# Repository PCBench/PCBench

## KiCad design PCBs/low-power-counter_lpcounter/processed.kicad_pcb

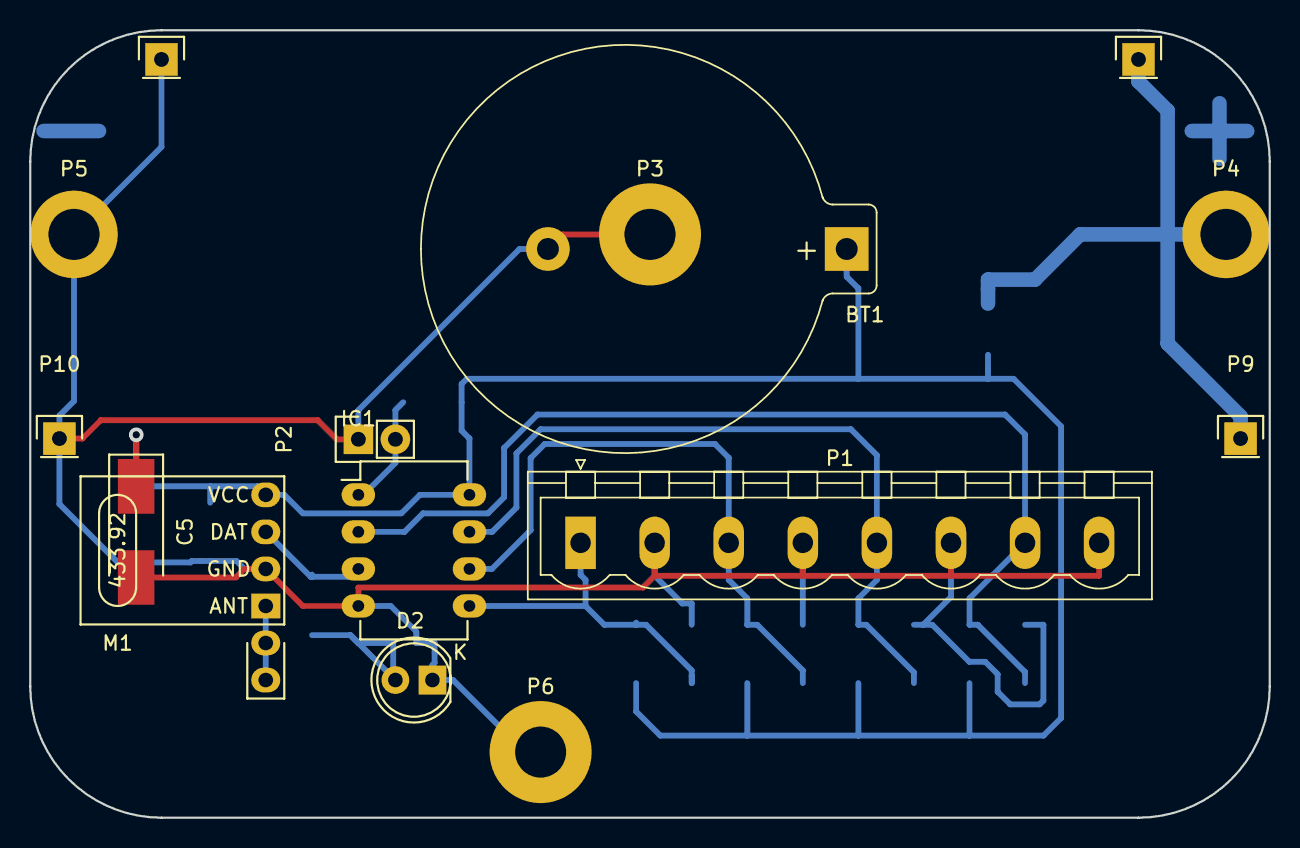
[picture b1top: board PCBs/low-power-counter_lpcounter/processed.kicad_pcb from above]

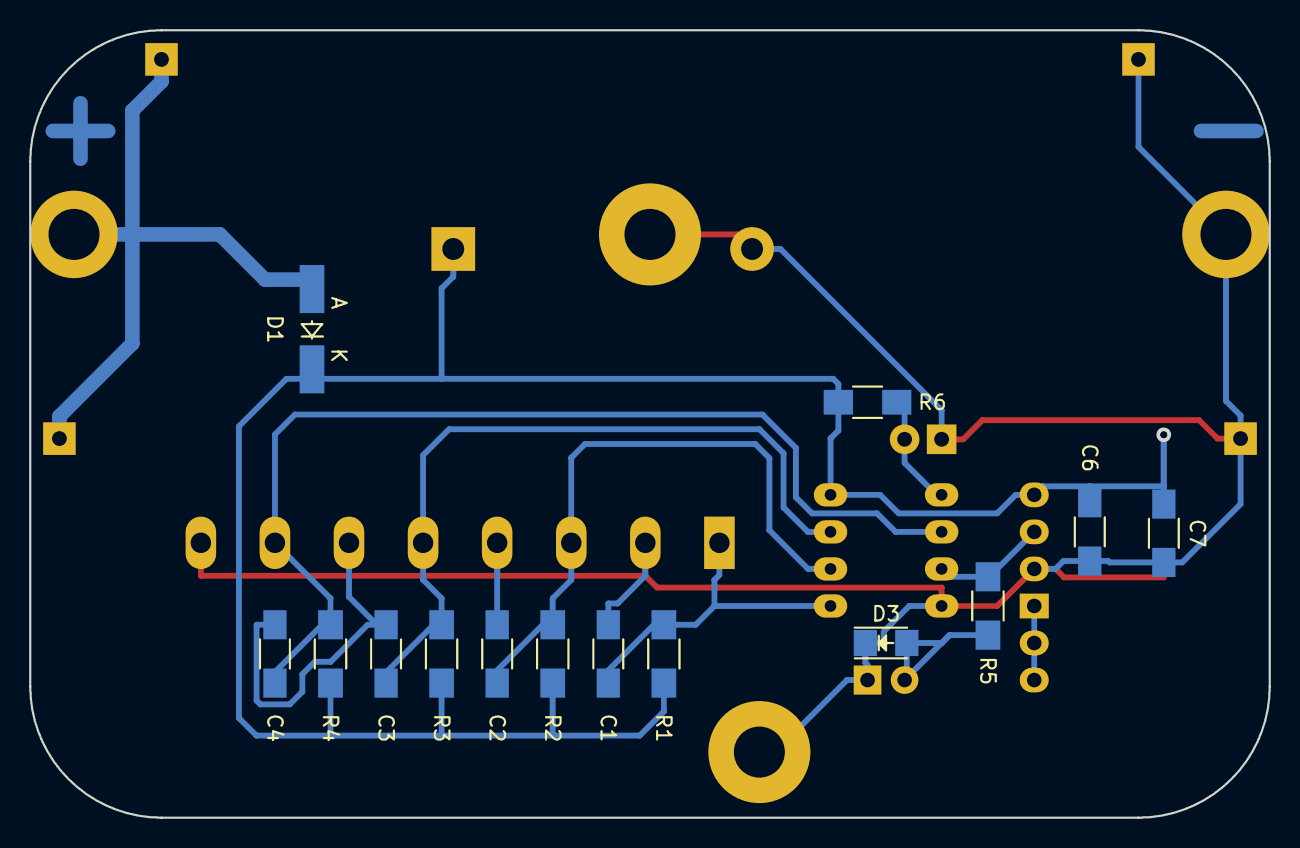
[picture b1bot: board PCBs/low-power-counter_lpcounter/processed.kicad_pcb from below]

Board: 2 copper layers, 85.0 x 54.0 mm, 29 parts (14 on the bottom side), 10 nets.

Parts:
BT1: CR2032; Keystone_106_1x20mm-CoinCell
C1, C2, C3, C4, C6, C7: 100nF; C_1206_HandSoldering
C5: 4.7uF; Tantalum_Case-U_EIA-6032-15_Hand
D1: 1N4148; MiniMELF_Handsoldering
D2: ORANGE; LED-5MM
D3: ORANGE; LED_1206
IC1: ATTINY85V-P; DIP-8_W7.62mm_LongPads
M1: SYN115
P1: CONN_01X08; PhoenixContact_MSTBVA-G_08x5.08mm_Vertical
P2: CONN_02X01; Pin_Header_Straight_1x02
P3, P4, P5, P6: Hole_3.5mm; MountingHole_3.5mm_Pad
P7, P9: BAT+; Pin_Header_Straight_1x01
P8, P10: BAT-; Pin_Header_Straight_1x01
R1, R2, R3, R4: 1M; R_1206_HandSoldering
R5: 1k; R_1206_HandSoldering
R6: 10k; R_1206_HandSoldering

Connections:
+3V3: BT1.1, C5.1, C6.1, C7.1, D1.1, IC1.8, M1.4, R1.1, R2.1, R3.1, R4.1, R6.1
/IN0: C1.1, IC1.5, P1.1, R1.2
/IN1: C2.1, IC1.6, P1.3, R2.2
/IN2: C3.1, IC1.7, P1.5, R3.2
/IN3: C4.1, IC1.2, P1.7, R4.2
/LED: D2.2, D3.2, R5.1
/OUT: IC1.3, M1.3, R5.2
/RESETn: IC1.1, P2.2, R6.2
/VBAT: D1.2, P4.1, P7.1, P9.1
GND: BT1.2, C1.2, C2.2, C3.2, C4.2, C5.2, C6.2, C7.2, D2.1, D3.1, IC1.4, M1.2, P1.2, P1.4, P1.6, P1.8, P2.1, P3.1, P5.1, P6.1, P8.1, P10.1

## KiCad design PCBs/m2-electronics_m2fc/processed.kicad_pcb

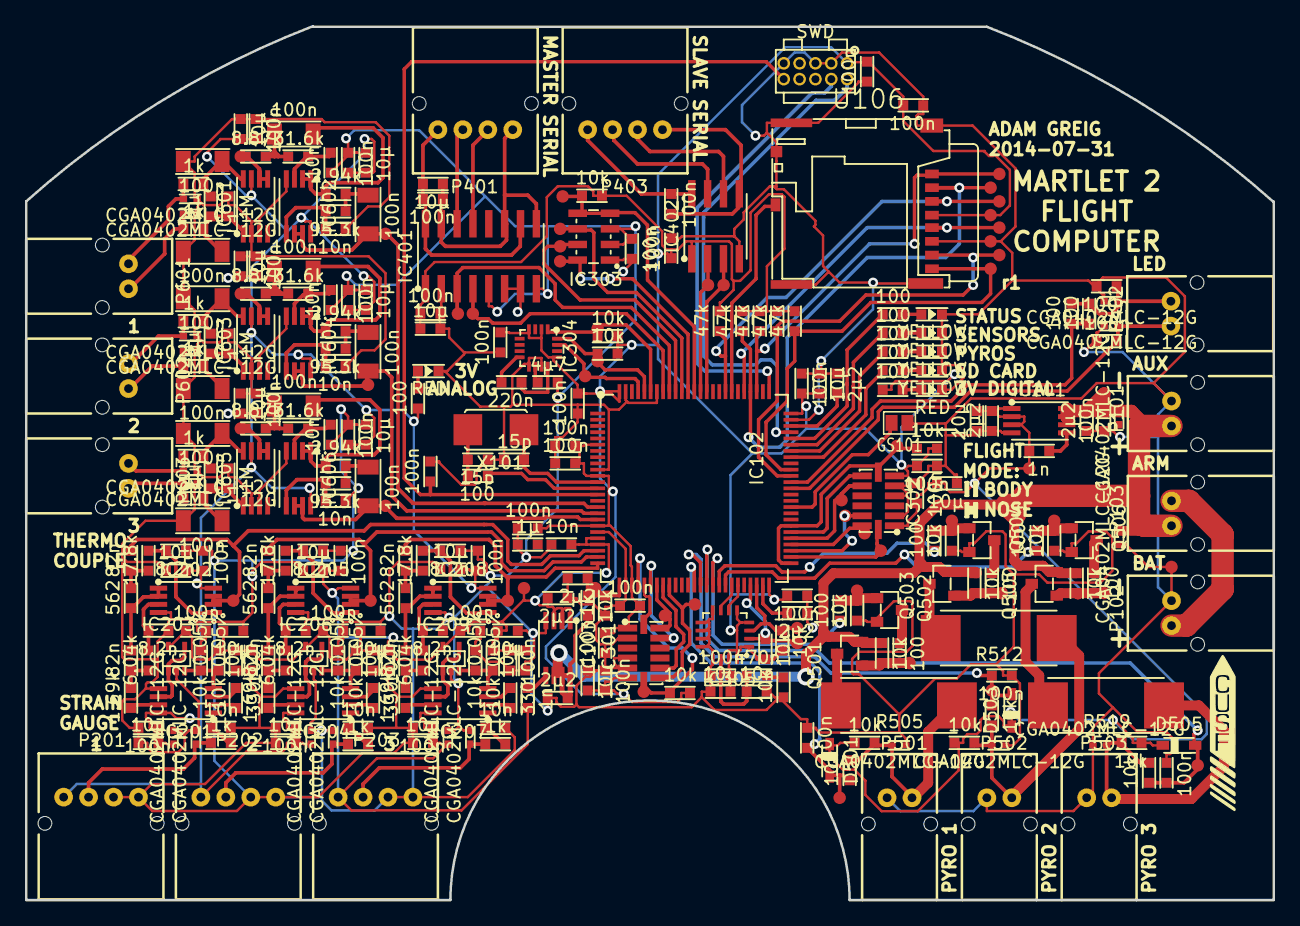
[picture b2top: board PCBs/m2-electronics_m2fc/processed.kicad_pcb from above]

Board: 4 copper layers, 100.0 x 70.0 mm, 345 parts (1 on the bottom side), 170 nets.

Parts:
C101, C104, C106, C119, C120, C124, C126: 2µ2; C0603
C102, C103, C108, C110, C111, C112, C113, C114, C115, C116, C122, C209, C210, C211, C212, C222, C223, C224, C225, C235, C236, C237, C238, C301, C302, C304, C305, C307, C308, C310, C403, C404, C405, C406, C407, C408, C501, C502, C503, C601, C604, C612, C615, C623, C626: 100n; C0603
C105, C125: 1n; C0603
C107, C109, C204, C205, C206, C213, C217, C218, C219, C226, C230, C231, C232, C239, C303, C306, C309, C401, C402, C602, C605, C613, C616, C624, C627: 10µ; C0603
C117, C608, C619, C630: 1µ; C0603
C118, C201, C214, C227, C311, C609, C610, C620, C621, C631, C632: 10n; C0603
C121, C123: 15p; C0603
C202, C203, C215, C216, C228, C229: 82n; C0603
C207, C208, C220, C221, C233, C234: 8.2n; C0603
C312: 220n; C0603
C313: 470n; C0603
C314: 4µ7; C0603
C603, C606, C607, C611, C614, C617, C618, C622, C625, C628, C629, C633: 100n; C1206
D101, D102, D201, D202, D203, D204, D205, D206, D406, D407, D502, D504, D506, D601, D602, D603, D604, D605, D606: CGA0402MLC-12G; R0402
D401, D408: RED; LED0603
D402, D403, D404, D405: YELLOW; LED0603
D501, D503, D505: DIODESCH; SOD323
GS101: GS2
IC101, IC103: ADP3335; MSOP8
IC102: STM32F405VGT; LQFP100
IC201, IC204, IC207: AD8226; MSOP8
IC202, IC205, IC208, IC602, IC604, IC606: AD8656; MSOP8
IC203, IC206, IC209: AD8541; SC-70-5
IC301: ADXL375; ADXL3x5
IC302: ADXL345; ADXL3x5
IC303: MS5611-01BA03; MS5611-01BA
IC304: HMC5883L
IC305: L3G4200D
IC401: ADuM5201; SOIC16
IC402: ADuM1201; SOIC8
IC601, IC603, IC605: AD8495; MSOP8
P101, P102, P103, P402, P501, P502, P503, P601, P602, P603: CONN_2; S02B-PASK-2
P104: SWD; FTSH-105-01-F-D-K
P201, P202, P203, P401, P403: CONN_4; S04B-PASK-2
Q501, Q503, Q505: MOSFET_P; SOT-23-MOSFET
Q502, Q504, Q506: MOSFET_N; SOT-23-MOSFET
R101, R301, R302, R303, R304, R305, R306, R307, R308, R501, R504, R506, R507, R508, R511, R513, R514, R515, R518, R520, R521: 10k; R0603
R102, R201, R209, R217, R601, R606, R608, R613, R615, R620: 1k; R0603
R103, R104, R105, R106, R107: 47k; R0603
R108, R401, R402, R403, R404, R405, R406, R407, R408, R502, R503, R509, R510, R516, R517: 100; R0603
R202, R208, R210, R216, R218, R224: 10k 0.05%; R0603
R203, R211, R219: 330; R0603
R204, R212, R220: 1.69k; R0603
R205, R213, R221: 6.04k; R0603
R206, R214, R222: 562; R0603
R207, R215, R223: 17.8k; R0603
R505, R512, R519: 5; PWR4318
R602, R609, R616: 8.87k; R0603
R603, R610, R617: 31.6k; R0603
R604, R611, R618: 2.94k; R0603
R605, R612, R619: 95.3k; R0603
R607, R614, R621: 1M; R0603
TP101, TP102, TP103, TP104, TP105, TP106, TP107, TP108, TP109, TP110, TP111, TP113, TP114, TP201, TP202, TP203, TP301, TP304, TP305, TP306, TP308, TP309, TP310, TP312, TP313, TP314, TP315, TP316, TP317, TP318, TP319, TP320, TP321, TP401, TP402, TP403, TP404, TP501, TP502, TP503, TP504, TP505, TP506, TP507, TP508, TP509, TP601, TP602, TP603, TP604, TP605, TP606: TESTPAD
U106: MICROSD
U113: LOGO; cusf_logo_full
U114: LOGO; cusf_logo_small
X101: 8M; XTAL50x32

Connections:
+3.3V: C103.1, C105.1, C106.1, C107.1, C108.1, C109.1, C110.1, C111.1, C112.1, C113.1, C114.1, C115.1, C116.1, C301.1, C302.1, C303.1, C304.1, C305.1, C306.1, C307.1, C308.1, C309.1, C310.1, C401.2, C403.2, C406.2, D501.2, D503.2, D505.2, IC101.1, IC101.2, IC101.3, IC102.6, IC102.11, IC102.19, IC102.28, IC102.50, IC102.75, IC102.100, IC301.1, IC301.6, IC302.1, IC302.6, IC303.1, IC304.2, IC304.4, IC304.13, IC305.1, IC305.4, IC305.5, IC305.15, IC305.16, IC401.1, IC401.6, IC401.7, IC402.1, P104.1, R103.1, R104.1, R105.1, R106.1, R107.1, R301.1, R302.1, R303.1, R304.1, R305.1, R306.1, R307.1, R401.2, R506.2, R513.2, R520.2, TP102.1, TP113.1, U106.4
+BATT: C102.1, C104.1, C124.1, D101.1, D102.1, IC101.6, IC101.7, IC101.8, IC103.6, IC103.7, IC103.8, P101.2, P103.2, Q501.S, Q503.S, Q505.S, R101.1, R501.2, R508.2, R515.2, TP104.1
/BAT_MON: C101.2, IC102.26, R101.2, R102.1, TP101.1
/IMU/BARO_CS: IC102.88, IC303.4, IC303.5, R307.2, TP321.1
/IMU/BARO_MISO: IC102.90, IC303.6, TP319.1
/IMU/BARO_MOSI: IC102.91, IC303.7, TP318.1
/IMU/BARO_SCK: IC102.89, IC303.8, TP317.1
/IMU/GYRO_DRDY: IC102.45, IC305.6
/IMU/GYRO_INT1: IC102.44, IC305.7
/IMU/GYRO_SCL: IC102.47, IC305.2, R305.2, TP313.1
/IMU/GYRO_SDA: IC102.48, IC305.3, R303.2, TP315.1
/IMU/HG_ACCEL_CS: IC102.29, IC301.7, R301.2, TP305.1
/IMU/HG_ACCEL_INT1: IC102.34, IC301.8, TP301.1
/IMU/HG_ACCEL_INT2: IC102.33, IC301.9
/IMU/HG_ACCEL_MISO: IC102.31, IC301.12
/IMU/HG_ACCEL_MOSI: IC102.32, IC301.13, TP309.1
/IMU/HG_ACCEL_SCK: IC102.30, IC301.14
/IMU/LG_ACCEL_CS: IC102.51, IC102.57, IC302.7, R302.2, TP306.1
/IMU/LG_ACCEL_INT1: IC102.56, IC302.8
/IMU/LG_ACCEL_INT2: IC102.55, IC302.9, TP304.1
/IMU/LG_ACCEL_MISO: IC102.53, IC302.12, TP308.1
/IMU/LG_ACCEL_MOSI: IC102.54, IC302.13, TP310.1
/IMU/LG_ACCEL_SCK: IC102.52, IC302.14, TP312.1
/IMU/MAGNO_DRDY: IC102.97, IC304.15, TP320.1
/IMU/MAGNO_SCL: IC102.95, IC304.1, R306.2, TP314.1
/IMU/MAGNO_SDA: IC102.96, IC304.16, R304.2, TP316.1
/IO/LED_1: IC102.68, R402.2
/IO/LED_2: IC102.69, R403.2
/IO/LED_3: IC102.70, R404.2
/IO/LED_4: IC102.71, R405.2
/IO/LED_A: IC102.64, R406.2, R407.2
/IO/LED_C: C407.1, D407.2, IC102.63, P402.2
/IO/SER_IN_1: IC102.93, IC401.4, TP402.1
/IO/SER_IN_2: IC102.87, IC402.2, TP403.1
/IO/SER_OUT_1: IC102.92, IC401.3, TP401.1
/IO/SER_OUT_2: IC102.86, IC402.3, TP404.1
/Pyros/PYRO_1_C: C501.1, D501.1, IC102.38, R507.2, TP503.1
/Pyros/PYRO_1_F: IC102.41, R502.2
/Pyros/PYRO_2_C: C502.1, D503.1, IC102.39, R514.2, TP506.1
/Pyros/PYRO_2_F: IC102.42, R509.2
/Pyros/PYRO_3_C: C503.1, D505.1, IC102.40, R521.2, TP509.1
/Pyros/PYRO_3_F: IC102.43, R516.2
/SD_CD: IC102.82, U106.11
/SD_CLK: IC102.80, TP110.1, U106.5
/SD_CMD: IC102.83, R107.2, TP109.1, U106.3
/SD_DAT0: IC102.65, R103.2, TP105.1, U106.7
/SD_DAT1: IC102.66, R104.2, TP106.1, U106.8
/SD_DAT2: IC102.78, R105.2, TP107.1, U106.1
/SD_DAT3: IC102.79, R106.2, TP108.1, U106.2
/SJ1: GS101.2, IC102.60
/SWCLK: IC102.76, P104.4
/SWDIO: IC102.72, P104.2
/StrainGauges/STRAIN_1: C203.1, IC102.23, IC202.6, IC202.7, TP201.1
/StrainGauges/STRAIN_2: C216.1, IC102.24, IC205.6, IC205.7, TP202.1
/StrainGauges/STRAIN_3: C229.1, IC102.25, IC208.6, IC208.7, TP203.1
/Thermocouples/THERMO_1: C607.1, IC102.16, IC602.6, IC602.7, TP602.1
/Thermocouples/THERMO_2: C618.1, IC102.17, IC604.6, IC604.7, TP604.1
/Thermocouples/THERMO_3: C629.1, IC102.18, IC606.6, IC606.7, TP606.1
/nRST: C122.2, IC102.14, P104.10
GND: C101.1, C102.2, C103.2, C104.2, C106.2, C107.2, C108.2, C109.2, C110.2, C111.2, C112.2, C113.2, C114.2, C115.2, C116.2, C117.2, C118.2, C119.2, C120.2, C121.2, C122.1, C123.2, C124.2, C126.2, C201.1, C204.2, C205.2, C206.2, C207.2, C208.2, C209.1, C210.1, C211.1, C212.2, C213.2, C214.1, C217.2, C218.2, C219.2, C220.2, C221.2, C222.1, C223.1, C224.1, C225.2, C226.2, C227.1, C230.2, C231.2, C232.2, C233.2, C234.2, C235.1, C236.1, C237.1, C238.2, C239.2, C301.2, C302.2, C303.2, C304.2, C305.2, C306.2, C307.2, C308.2, C309.2, C310.2, C311.1, C314.1, C401.1, C403.1, C405.1, C406.1, C407.2, C501.2, C502.2, C503.2, C601.2, C602.2, C603.1, C604.2, C605.2, C609.2, C610.2, C611.1, C612.2, C613.2, C614.1, C615.2, C616.2, C620.2, C621.2, C622.1, C623.2, C624.2, C625.1, C626.2, C627.2, C631.2, C632.2, C633.1, D101.2, D102.2, D201.1, D202.1, D203.1, D204.1, D205.1, D206.1, D401.2, D402.2, D403.2, D404.2, D405.2, D406.1, D407.1, D408.2, D502.2, D504.2, D506.2, D601.2, D602.2, D603.2, D604.2, D605.2, D606.2, GS101.1, IC101.4, IC102.10, IC102.20, IC102.27, IC102.74, IC102.94, IC102.99, IC103.4, IC201.5, IC202.4, IC203.2, IC204.5, IC205.4, IC206.2, IC207.5, IC208.4, IC209.2, IC301.2, IC301.4, IC301.5, IC302.2, IC302.4, IC302.5, IC303.2, IC303.3, IC304.9, IC304.11, IC305.8, IC305.9, IC305.10, IC305.11, IC305.12, IC305.13, IC401.2, IC401.5, IC401.8, IC402.4, IC601.2, IC601.3, IC602.4, IC603.2, IC603.3, IC604.4, IC605.2, IC605.3, IC606.4, P101.1, P102.1, P104.3, P104.5, P104.9, P201.1, P201.2, P202.1, P202.2, P203.1, P203.2, P501.2, P502.2, P503.2, Q502.S, Q504.S, Q506.S, R102.2, R208.2, R216.2, R224.2, R308.2, R504.2, R511.2, R518.2, R607.2, R614.2, R621.2, TP103.1, TP114.1, U106.6, U106.9, U106.10
unnamed: C105.2, IC101.5
unnamed: C119.1, IC102.49
unnamed: C120.1, IC102.73
unnamed: C121.1, IC102.12, X101.1
unnamed: C123.1, R108.1, X101.2
unnamed: C125.2, IC103.5
unnamed: C201.2, IC201.1, R201.1
unnamed: C202.1, IC202.1, IC202.2, R206.2
unnamed: C202.2, R204.1, R205.2
unnamed: C203.2, R206.1, R207.2
unnamed: C207.1, IC202.3, R205.1
unnamed: C208.1, IC202.5, R207.1
unnamed: C214.2, IC204.1, R209.1
unnamed: C215.1, IC205.1, IC205.2, R214.2
unnamed: C215.2, R212.1, R213.2
unnamed: C216.2, R214.1, R215.2
unnamed: C220.1, IC205.3, R213.1
unnamed: C221.1, IC205.5, R215.1
unnamed: C227.2, IC207.1, R217.1
unnamed: C228.1, IC208.1, IC208.2, R222.2
unnamed: C228.2, R220.1, R221.2
unnamed: C229.2, R222.1, R223.2
unnamed: C233.1, IC208.3, R221.1
unnamed: C234.1, IC208.5, R223.1
unnamed: C311.2, C313.2, IC305.14
unnamed: C312.1, IC304.8
unnamed: C312.2, IC304.12
unnamed: C313.1, R308.1
unnamed: C314.2, IC304.10
unnamed: C402.1, C404.1, IC401.10, IC401.16, P401.1
unnamed: C402.2, C404.2, IC401.9, IC401.11, IC401.15, P401.4
unnamed: C405.2, D406.2, P402.1, R406.1, R407.1
unnamed: C408.1, IC402.5, P403.4
unnamed: C408.2, IC402.8, P403.1
unnamed: C603.2, C608.1, IC601.8, R601.1
unnamed: C606.1, IC602.1, IC602.2, R604.2
unnamed: C606.2, R602.1, R603.2
unnamed: C607.2, R604.1, R605.2
unnamed: C608.2, C611.2, IC601.1, R606.1, R607.1
unnamed: C609.1, IC602.3, R603.1
unnamed: C610.1, IC602.5, R605.1
unnamed: C614.2, C619.1, IC603.8, R608.1
unnamed: C617.1, IC604.1, IC604.2, R611.2
unnamed: C617.2, R609.1, R610.2
unnamed: C618.2, R611.1, R612.2
unnamed: C619.2, C622.2, IC603.1, R613.1, R614.1
unnamed: C620.1, IC604.3, R610.1
unnamed: C621.1, IC604.5, R612.1
unnamed: C625.2, C630.1, IC605.8, R615.1
unnamed: C628.1, IC606.1, IC606.2, R618.2
unnamed: C628.2, R616.1, R617.2
unnamed: C629.2, R618.1, R619.2
unnamed: C630.2, C633.2, IC605.1, R620.1, R621.1
unnamed: C631.1, IC606.3, R617.1
unnamed: C632.1, IC606.5, R619.1
unnamed: D202.2, P201.3, R201.2
unnamed: D204.2, P202.3, R209.2
unnamed: D206.2, P203.3, R217.2
unnamed: D401.1, R401.1
unnamed: D402.1, R402.1
unnamed: D403.1, R403.1
unnamed: D404.1, R404.1
unnamed: D405.1, R405.1
unnamed: D408.1, R408.1
unnamed: D502.1, P501.1, R505.1, R506.1, R507.1
unnamed: D504.1, P502.1, R512.1, R513.1, R514.1
unnamed: D506.1, P503.1, R519.1, R520.1, R521.1
unnamed: D601.1, P601.2, R601.2
unnamed: D602.1, P601.1, R606.2
unnamed: D603.1, P602.2, R608.2
unnamed: D604.1, P602.1, R613.2
unnamed: D605.1, P603.2, R615.2
unnamed: D606.1, P603.1, R620.2
unnamed: IC102.13, R108.2
unnamed: IC201.2, R203.1
unnamed: IC201.3, R203.2
unnamed: IC201.4, IC203.3, R202.2, R208.1
unnamed: IC201.6, IC203.1, IC203.4
unnamed: IC201.7, R204.2
unnamed: IC204.2, R211.1
unnamed: IC204.3, R211.2
unnamed: IC204.4, IC206.3, R210.2, R216.1
unnamed: IC204.6, IC206.1, IC206.4
unnamed: IC204.7, R212.2
unnamed: IC207.2, R219.1
unnamed: IC207.3, R219.2
unnamed: IC207.4, IC209.3, R218.2, R224.1
unnamed: IC207.6, IC209.1, IC209.4
unnamed: IC207.7, R220.2
unnamed: IC401.13, P401.3
unnamed: IC401.14, P401.2
unnamed: IC402.6, P403.3
unnamed: IC402.7, P403.2
unnamed: IC601.5, IC601.6, R602.2, TP601.1
unnamed: IC603.5, IC603.6, R609.2, TP603.1
unnamed: IC605.5, IC605.6, R616.2, TP605.1
unnamed: P102.2, P103.1
unnamed: Q501.D, R505.2
unnamed: Q501.G, R501.1, R503.1, TP501.1
unnamed: Q502.D, R503.2
unnamed: Q502.G, R502.1, R504.1, TP502.1
unnamed: Q503.D, R512.2
unnamed: Q503.G, R508.1, R510.1, TP504.1
unnamed: Q504.D, R510.2
unnamed: Q504.G, R509.1, R511.1, TP505.1
unnamed: Q505.D, R519.2
unnamed: Q505.G, R515.1, R517.1, TP507.1
unnamed: Q506.D, R517.2
unnamed: Q506.G, R516.1, R518.1, TP508.1
VAA: C118.1, C125.1, C126.1, C204.1, C205.1, C206.1, C209.2, C210.2, C211.2, C212.1, C213.1, C217.1, C218.1, C219.1, C222.2, C223.2, C224.2, C225.1, C226.1, C230.1, C231.1, C232.1, C235.2, C236.2, C237.2, C238.1, C239.1, C601.1, C602.1, C604.1, C605.1, C612.1, C613.1, C615.1, C616.1, C623.1, C624.1, C626.1, C627.1, D201.2, D203.2, D205.2, IC102.21, IC102.22, IC103.1, IC103.2, IC103.3, IC201.8, IC202.8, IC203.5, IC204.8, IC205.8, IC206.5, IC207.8, IC208.8, IC209.5, IC601.7, IC602.8, IC603.7, IC604.8, IC605.7, IC606.8, P201.4, P202.4, P203.4, R202.1, R210.1, R218.1, R408.2, TP111.1

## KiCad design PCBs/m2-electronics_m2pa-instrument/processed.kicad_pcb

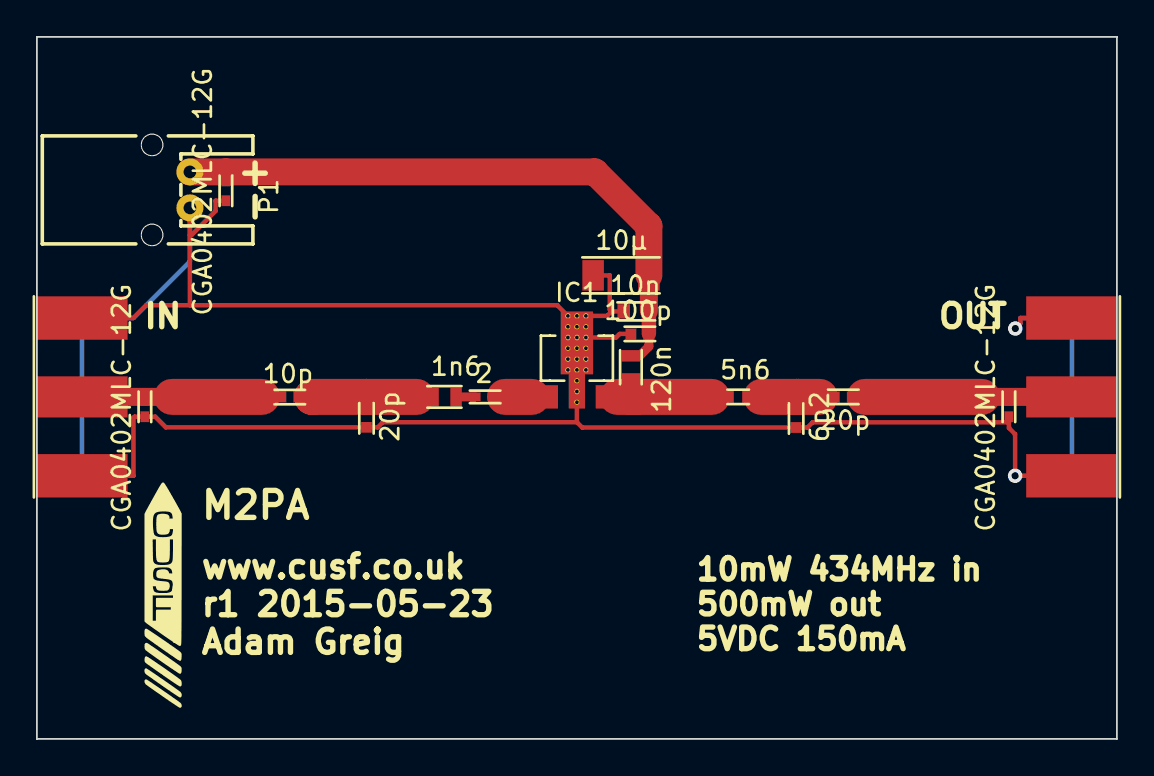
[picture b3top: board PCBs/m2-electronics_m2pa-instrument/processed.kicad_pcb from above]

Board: 2 copper layers, 60.0 x 39.0 mm, 18 parts (0 on the bottom side), 9 nets.

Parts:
C1: 10p; C0402
C2, C7: 20p; C0402
C3: 100p; C0402
C4: 10n; C0603
C5: 6p2; C0402
C6: 10µ; C1206
D1, D2, D3: CGA0402MLC-12G; R0402
IC1: ADL5324; SOT89-3
L1: 1n6; L0603
L2: 120n; L0603
L3: 5n6; L0402
P1: CONN_01X02; S02B-PASK-2
P2, P3: SMA; SMA-142-0701-801
R1: 2; R0402

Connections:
+5V: C3.1, C4.1, C6.1, D3.1, L2.2, P1.2
GND: C2.1, C3.2, C4.2, C5.1, C6.2, D1.2, D2.2, D3.2, IC1.2, P1.1, P2.2, P2.3, P2.4, P2.5, P3.2, P3.3, P3.4, P3.5
unnamed: C1.1, C2.2, L1.2
unnamed: C1.2, D1.1, P2.1
unnamed: C5.2, C7.1, L3.1
unnamed: C7.2, D2.1, P3.1
unnamed: IC1.1, R1.1
unnamed: IC1.3, L2.1, L3.2
unnamed: L1.1, R1.2

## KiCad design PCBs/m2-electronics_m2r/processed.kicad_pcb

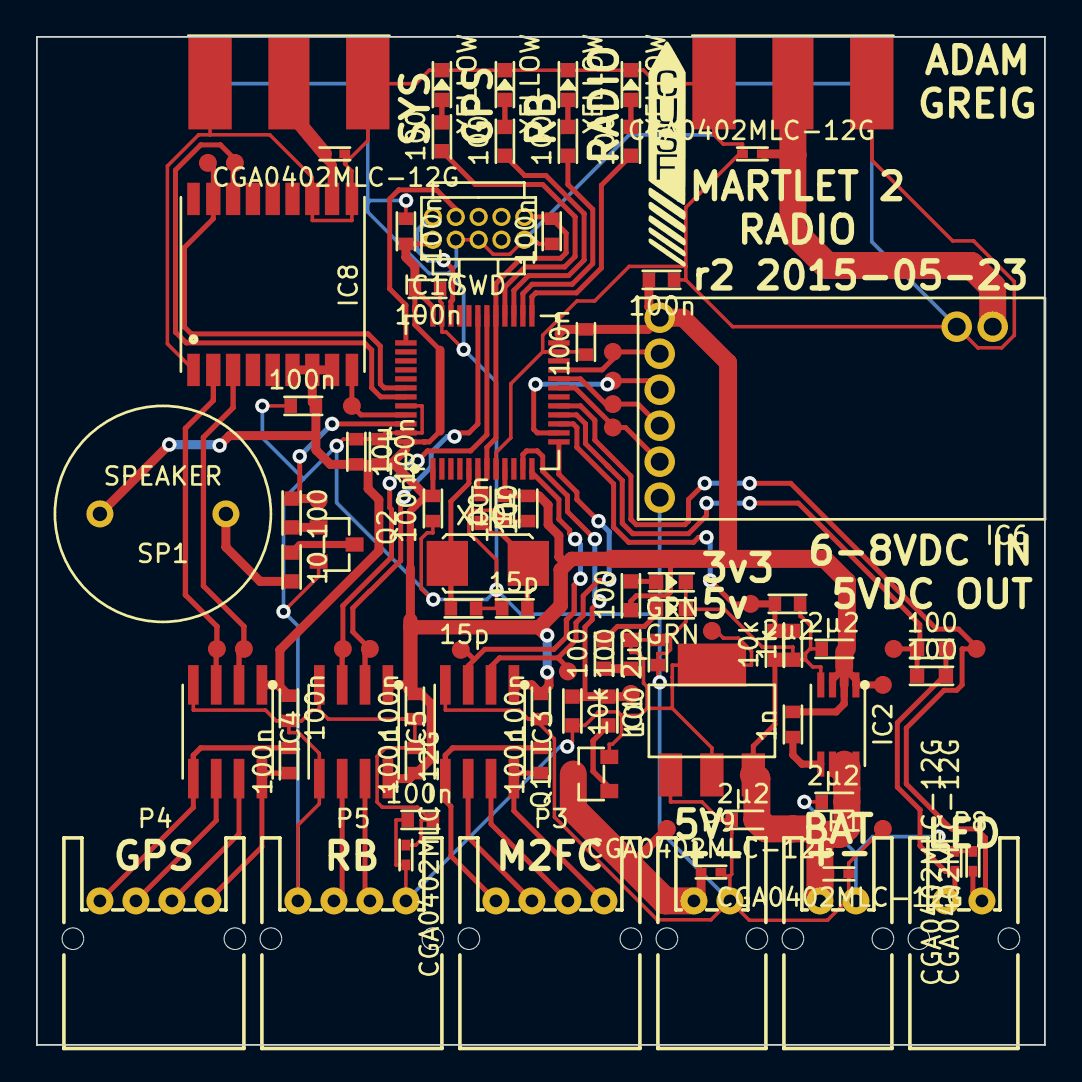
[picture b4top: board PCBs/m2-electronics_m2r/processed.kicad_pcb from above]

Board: 2 copper layers, 56.0 x 56.0 mm, 99 parts (0 on the bottom side), 58 nets.

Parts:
C1, C2, C3, C4, C5, C6, C11, C14, C15, C24, C25, C26, C27, C29, C30, C34: 100n; C0603
C7, C8, C9, C10, C13: 2µ2; C0603
C12: 1n; C0603
C23: 10µ; C0603
C28: 1µ; C0603
C35, C36: 15p; C0603
D1, D2: GRN; LED0603
D3, D4, D5, D6: YELLOW; LED0603
D7, D8, D9, D10, D11, D12, D13: CGA0402MLC-12G; R0402
IC1: ADP3338; SOT223
IC2: ADP3335; MSOP8
IC3, IC4, IC5: ADuM1201; SOIC8
IC6: MTX2
IC8: MAX-7Q
IC10: STM32F303C; LQFP48
P1, P8, P9: CONN_2; S02B-PASK-2
P2, P7: SMA; SMA-142-0701-801
P3, P4, P5: CONN_4; S04B-PASK-2
P6: SWD; FTSH-105-01-F-D-K
Q1: Q_PMOS_GSD_PSV; SOT-23
Q2: Q_NMOS_GSD_PSV; SOT-23
R1, R3: 10k; R0603
R2: 1k; R0603
R4, R5, R7, R8, R9, R10, R11, R12, R13, R14, R15, R16: 100; R0603
R6: 10; R0603
SP1: SPEAKER; ABI-042-RC
TP1, TP2, TP4, TP7, TP11, TP12, TP13, TP14, TP15, TP16, TP17, TP18, TP19, TP20, TP21, TP22, TP23, TP24, TP25, TP26, TP27, TP28, TP29: TESTPAD
X10: 8M; XTAL50x32

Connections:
5V_OUT: IC10.11, R3.2, R16.2, TP27.1
+3V3: C3.2, C5.2, C6.1, C8.1, C11.1, C12.1, C14.1, C15.1, C23.1, C24.1, C25.1, C26.1, C27.1, C28.1, C29.1, C30.1, IC2.1, IC2.2, IC2.3, IC3.1, IC4.1, IC5.1, IC5.8, IC6.3, IC8.6, IC8.7, IC8.8, IC10.1, IC10.9, IC10.24, IC10.36, IC10.48, P6.1, R8.2, SP1.1, TP1.1
+5V: C4.2, C10.1, D7.1, IC1.2, P5.1, Q1.2, R3.1, R9.1, TP2.1
+BATT: C7.1, C9.1, D8.1, IC1.3, IC2.6, IC2.7, IC2.8, P1.2, R1.2, TP11.1
BAT_MON: C13.1, IC10.15, R1.1, R2.1, TP13.1
BUZZER: IC10.46, R15.2, TP28.1
GND: C3.1, C4.1, C5.1, C6.2, C7.2, C8.2, C9.2, C10.2, C11.2, C13.2, C14.2, C15.2, C23.2, C24.2, C25.2, C26.2, C27.2, C28.2, C29.2, C30.2, C34.2, C35.2, C36.2, D1.2, D2.2, D3.2, D4.2, D5.2, D6.2, D7.2, D8.2, D9.2, D10.1, D11.1, D12.2, D13.1, IC1.1, IC2.4, IC3.4, IC4.4, IC5.4, IC5.5, IC6.2, IC6.8, IC8.1, IC8.10, IC8.12, IC10.8, IC10.23, IC10.35, IC10.44, IC10.47, P1.1, P2.2, P2.3, P2.4, P2.5, P5.4, P6.3, P6.5, P6.9, P7.2, P7.3, P7.4, P7.5, P9.1, Q2.2, R2.2, TP12.1
GPS_RESET: IC8.9, IC10.45, TP19.1
GPS_RX: IC4.2, IC8.3, TP4.1
GPS_SCL: IC8.17, IC10.42, TP20.1
GPS_SDA: IC8.16, IC10.43, TP21.1
GPS_TX: IC4.3, IC8.2, TP7.1
LED_1: IC10.25, R10.2
LED_2: IC10.26, R12.2
LED_3: IC10.27, R11.2
LED_4: IC10.28, R13.2
LED_A: IC10.16, R4.2, R5.2, TP18.1
LED_C: D11.2, IC10.17, P8.1, TP26.1
NTX2B_EN: IC6.4, IC10.21, TP22.1
NTX2B_P0: IC6.7, IC10.19, TP25.1
NTX2B_P1: IC6.6, IC10.20, TP24.1
NTX2B_TXD: IC6.5, IC10.14, TP23.1
unnamed: C1.1, IC4.5, P4.4
unnamed: C1.2, IC4.8, P4.1
unnamed: C2.1, IC3.5, P3.4
unnamed: C2.2, IC3.8, P3.1
unnamed: C12.2, IC2.5
unnamed: C35.1, IC10.5, X10.1
unnamed: C36.1, R14.1, X10.2
unnamed: D1.1, R8.1
unnamed: D2.1, R7.1
unnamed: D3.1, R10.1
unnamed: D4.1, R11.1
unnamed: D5.1, R12.1
unnamed: D6.1, R13.1
unnamed: D9.1, IC6.1, P7.1
unnamed: D10.2, P8.2, R4.1, R5.1
unnamed: D12.1, IC8.11, P2.1
unnamed: D13.2, P9.2, Q1.3, TP29.1
unnamed: IC3.6, P3.3
unnamed: IC3.7, P3.2
unnamed: IC4.6, P4.3
unnamed: IC4.7, P4.2
unnamed: IC5.6, P5.3
unnamed: IC5.7, P5.2
unnamed: IC10.6, R14.2
unnamed: Q1.1, R16.1
unnamed: Q2.1, R15.1
unnamed: Q2.3, R6.2
unnamed: R6.1, SP1.2
unnamed: R7.2, R9.2
RB_RX: IC5.3, IC10.30, TP14.1
RB_TX: IC5.2, IC10.31, TP15.1
SER_IN: IC3.2, IC10.13, TP17.1
SER_OUT: IC3.3, IC10.12, TP16.1
SWCLK: IC10.37, P6.4
SWDIO: IC10.34, P6.2
nRST: C34.1, IC10.7, IC10.29, P6.10
